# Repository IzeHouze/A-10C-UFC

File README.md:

# A-10C-UFC
DCS A-10C UFC

This project is basically a home grown attempt to create a functional UFC for the A-10C module of the flight sim DCS World.
It is based on a simple 6x6 keyboard matrix interfaced to the PC via an Arduino Microcontroller.  There are the wiring scematics, a PCB layout and Blender files for an enclosure which should be 3D printable.

The PCB has sockets for plug in capability of either the Uno or Nano variety of Arduino Controller.

The code was originally created to work specifically for the A-10C module, however, since the F/A-18 simulation also has a UFC, there is an optional connection for a switch which can be used to change modes between the A-10 and the F-18.  There is also a connector for an external reset switch, which would be best used once you change aircraft modes, reset the controller to have it reboot into the correct mode.

The required software would be:
  DCS-BIOS, preferably the branch that includes the F/A-18 support
  Arduino Studio
      Keypad Library for Arduino - Authors:  Mark Stanley, Alexander Brevig
      DCS-BIOS-Arduino Library 
        Original version - http://dcs-bios.a10c.de/
        Branch with F/A-18 support - https://forums.eagle.ru/showthread.php?t=210960
        
Optional software would be:
  KiCAD - for the schematics and PCB layout
  Blender - for the 3D printable components of an enclosure

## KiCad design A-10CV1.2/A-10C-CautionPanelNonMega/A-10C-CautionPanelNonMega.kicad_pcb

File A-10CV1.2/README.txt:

This is designed in KiCAD 5.0.4

Front panel included using Front Panel Designer.

Both of these applications are free.

These are as-is and are not guaranteed.

In fact this is the 1.1 revision.
A noob mistake I found was that you cannot use Digital pins 0 and 1 if you use this card on a serial 
port, as those are Transmit and Receive for the USB COM port.

I have revised the schematics and layout to move those IOs to A0 and A1 on J3.

I have also added in the connections for a NANO.

And two JST connectors for an external reset button and a Mode selector switch for A-10 and F-18.

Happy BRRRRTing!

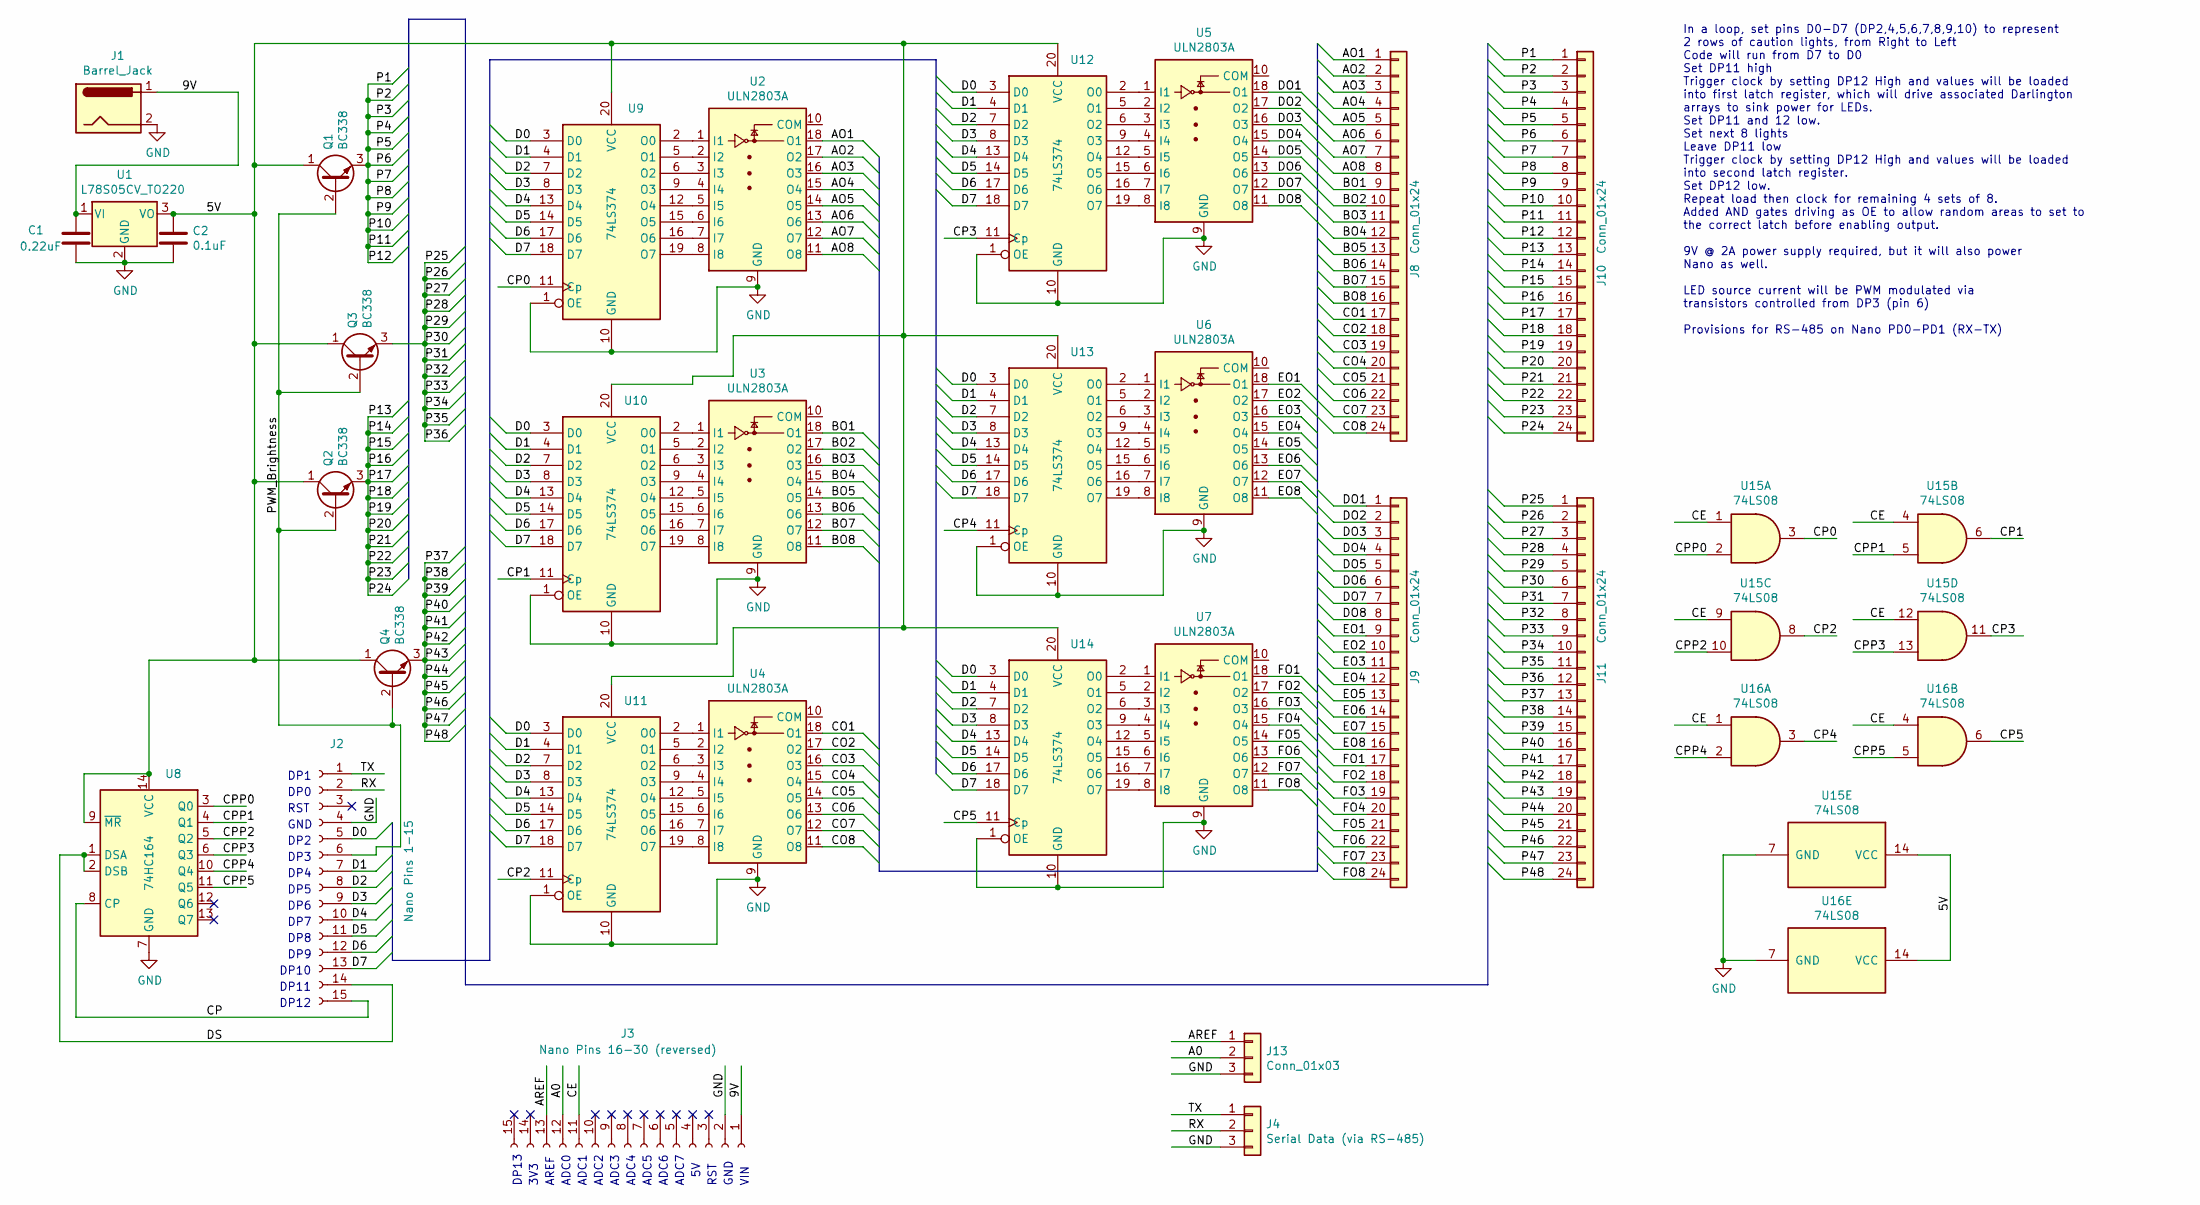
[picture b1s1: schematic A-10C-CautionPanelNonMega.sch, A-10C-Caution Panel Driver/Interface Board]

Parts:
C1: 0.22uF; C_Disc_D3.0mm_W2.0mm_P2.50mm
C2: 0.1uF; C_Disc_D3.0mm_W2.0mm_P2.50mm
J1: Barrel_Jack; BarrelJack_CUI_PJ-102AH_Horizontal
J2: Nano Pins 1-15; PinSocket_1x15_P2.54mm_Vertical
J3: Nano Pins 16-30 (reversed); PinSocket_1x15_P2.54mm_Vertical
J4: Serial Data (via RS-485); PinHeader_1x03_P2.54mm_Vertical
J8, J9, J10, J11: Conn_01x24; PinHeader_1x24_P2.54mm_Vertical
J13: Conn_01x03; PinHeader_1x03_P2.54mm_Vertical
Q1, Q2, Q3, Q4: BC338; TO-92_Inline
U1: L78S05CV_TO220; TO-220-3_Vertical
U2, U3, U4, U5, U6, U7: ULN2803A; DIP-18_W7.62mm
U8: 74HC164; DIP-14_W7.62mm
U9, U10, U11, U12, U13, U14: 74LS374; DIP-20_W7.62mm
U15, U16: 74LS08; DIP-14_W7.62mm

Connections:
/5V: C2.1, Q1.1 (C), Q2.1 (C), Q3.1 (C), Q4.1 (C), U1.3 (VO), U8.9 (~MR), U8.14 (VCC), U9.20 (VCC), U10.20 (VCC), U11.20 (VCC), U12.20 (VCC), U13.20 (VCC), U14.20 (VCC), U15.14 (VCC), U16.14 (VCC)
/9V: C1.1, J1.1, J3.1, U1.1 (VI)
/A0: J3.12, J13.2
/AO1: J8.1, U2.18 (O1)
/AO2: J8.2, U2.17 (O2)
/AO3: J8.3, U2.16 (O3)
/AO4: J8.4, U2.15 (O4)
/AO5: J8.5, U2.14 (O5)
/AO6: J8.6, U2.13 (O6)
/AO7: J8.7, U2.12 (O7)
/AO8: J8.8, U2.11 (O8)
/AREF: J3.13, J13.1
/BO1: J8.9, U3.18 (O1)
/BO2: J8.10, U3.17 (O2)
/BO3: J8.11, U3.16 (O3)
/BO4: J8.12, U3.15 (O4)
/BO5: J8.13, U3.14 (O5)
/BO6: J8.14, U3.13 (O6)
/BO7: J8.15, U3.12 (O7)
/BO8: J8.16, U3.11 (O8)
/CE: J3.11, U15.1, U15.4, U15.9, U15.12, U16.1, U16.4
/CO1: J8.17, U4.18 (O1)
/CO2: J8.18, U4.17 (O2)
/CO3: J8.19, U4.16 (O3)
/CO4: J8.20, U4.15 (O4)
/CO5: J8.21, U4.14 (O5)
/CO6: J8.22, U4.13 (O6)
/CO7: J8.23, U4.12 (O7)
/CO8: J8.24, U4.11 (O8)
/CP: J2.15, U8.8 (CP)
/CP0: U9.11 (Cp), U15.3
/CP1: U10.11 (Cp), U15.6
/CP2: U11.11 (Cp), U15.8
/CP3: U12.11 (Cp), U15.11
/CP4: U13.11 (Cp), U16.3
/CP5: U14.11 (Cp), U16.6
/CPP0: U8.3 (Q0), U15.2
/CPP1: U8.4 (Q1), U15.5
/CPP2: U8.5 (Q2), U15.10
/CPP3: U8.6 (Q3), U15.13
/CPP4: U8.10 (Q4), U16.2
/CPP5: U8.11 (Q5), U16.5
/D0: J2.5, U9.3 (D0), U10.3 (D0), U11.3 (D0), U12.3 (D0), U13.3 (D0), U14.3 (D0)
/D1: J2.7, U9.4 (D1), U10.4 (D1), U11.4 (D1), U12.4 (D1), U13.4 (D1), U14.4 (D1)
/D2: J2.8, U9.7 (D2), U10.7 (D2), U11.7 (D2), U12.7 (D2), U13.7 (D2), U14.7 (D2)
/D3: J2.9, U9.8 (D3), U10.8 (D3), U11.8 (D3), U12.8 (D3), U13.8 (D3), U14.8 (D3)
/D4: J2.10, U9.13 (D4), U10.13 (D4), U11.13 (D4), U12.13 (D4), U13.13 (D4), U14.13 (D4)
/D5: J2.11, U9.14 (D5), U10.14 (D5), U11.14 (D5), U12.14 (D5), U13.14 (D5), U14.14 (D5)
/D6: J2.12, U9.17 (D6), U10.17 (D6), U11.17 (D6), U12.17 (D6), U13.17 (D6), U14.17 (D6)
/D7: J2.13, U9.18 (D7), U10.18 (D7), U11.18 (D7), U12.18 (D7), U13.18 (D7), U14.18 (D7)
/DO1: J9.1, U5.18 (O1)
/DO2: J9.2, U5.17 (O2)
/DO3: J9.3, U5.16 (O3)
/DO4: J9.4, U5.15 (O4)
/DO5: J9.5, U5.14 (O5)
/DO6: J9.6, U5.13 (O6)
/DO7: J9.7, U5.12 (O7)
/DO8: J9.8, U5.11 (O8)
/DS: J2.14, U8.1 (DSA), U8.2 (DSB)
/EO1: J9.9, U6.18 (O1)
/EO2: J9.10, U6.17 (O2)
/EO3: J9.11, U6.16 (O3)
/EO4: J9.12, U6.15 (O4)
/EO5: J9.13, U6.14 (O5)
/EO6: J9.14, U6.13 (O6)
/EO7: J9.15, U6.12 (O7)
/EO8: J9.16, U6.11 (O8)
/FO1: J9.17, U7.18 (O1)
/FO2: J9.18, U7.17 (O2)
/FO3: J9.19, U7.16 (O3)
/FO4: J9.20, U7.15 (O4)
/FO5: J9.21, U7.14 (O5)
/FO6: J9.22, U7.13 (O6)
/FO7: J9.23, U7.12 (O7)
/FO8: J9.24, U7.11 (O8)
/P1: J10.1, J10.2, J10.3, J10.4, J10.5, J10.6, J10.7, J10.8, J10.9, J10.10, J10.11, J10.12, Q1.3 (E)
/P13: J10.13, J10.14, J10.15, J10.16, J10.17, J10.18, J10.19, J10.20, J10.21, J10.22, J10.23, J10.24, Q2.3 (E)
/P25: J11.1, J11.2, J11.3, J11.4, J11.5, J11.6, J11.7, J11.8, J11.9, J11.10, J11.11, J11.12, Q3.3 (E)
/P37: J11.13, J11.14, J11.15, J11.16, J11.17, J11.18, J11.19, J11.20, J11.21, J11.22, J11.23, J11.24, Q4.3 (E)
/PWM_Brightness: J2.6, Q1.2 (B), Q2.2 (B), Q3.2 (B), Q4.2 (B)
/RX: J2.2, J4.2
/TX: J2.1, J4.1
GND: C1.2, C2.2, J1.2, J2.4, J3.2, J4.3, J13.3, U1.2 (GND), U2.9 (GND), U3.9 (GND), U4.9 (GND), U5.9 (GND), U6.9 (GND), U7.9 (GND), U8.7 (GND), U9.1 (OE), U9.10 (GND), U10.1 (OE), U10.10 (GND), U11.1 (OE), U11.10 (GND), U12.1 (OE), U12.10 (GND), U13.1 (OE), U13.10 (GND), U14.1 (OE), U14.10 (GND), U15.7 (GND), U16.7 (GND)
unnamed: U2.1 (I1), U9.2 (O0)
unnamed: U2.2 (I2), U9.5 (O1)
unnamed: U2.3 (I3), U9.6 (O2)
unnamed: U2.4 (I4), U9.9 (O3)
unnamed: U2.5 (I5), U9.12 (O4)
unnamed: U2.6 (I6), U9.15 (O5)
unnamed: U2.7 (I7), U9.16 (O6)
unnamed: U2.8 (I8), U9.19 (O7)
unnamed: U3.1 (I1), U10.2 (O0)
unnamed: U3.2 (I2), U10.5 (O1)
unnamed: U3.3 (I3), U10.6 (O2)
unnamed: U3.4 (I4), U10.9 (O3)
unnamed: U3.5 (I5), U10.12 (O4)
unnamed: U3.6 (I6), U10.15 (O5)
unnamed: U3.7 (I7), U10.16 (O6)
unnamed: U3.8 (I8), U10.19 (O7)
unnamed: U4.1 (I1), U11.2 (O0)
unnamed: U4.2 (I2), U11.5 (O1)
unnamed: U4.3 (I3), U11.6 (O2)
unnamed: U4.4 (I4), U11.9 (O3)
unnamed: U4.5 (I5), U11.12 (O4)
unnamed: U4.6 (I6), U11.15 (O5)
unnamed: U4.7 (I7), U11.16 (O6)
unnamed: U4.8 (I8), U11.19 (O7)
unnamed: U5.1 (I1), U12.2 (O0)
unnamed: U5.2 (I2), U12.5 (O1)
unnamed: U5.3 (I3), U12.6 (O2)
unnamed: U5.4 (I4), U12.9 (O3)
unnamed: U5.5 (I5), U12.12 (O4)
unnamed: U5.6 (I6), U12.15 (O5)
unnamed: U5.7 (I7), U12.16 (O6)
unnamed: U5.8 (I8), U12.19 (O7)
unnamed: U6.1 (I1), U13.2 (O0)
unnamed: U6.2 (I2), U13.5 (O1)
unnamed: U6.3 (I3), U13.6 (O2)
unnamed: U6.4 (I4), U13.9 (O3)
unnamed: U6.5 (I5), U13.12 (O4)
unnamed: U6.6 (I6), U13.15 (O5)
unnamed: U6.7 (I7), U13.16 (O6)
unnamed: U6.8 (I8), U13.19 (O7)
unnamed: U7.1 (I1), U14.2 (O0)
unnamed: U7.2 (I2), U14.5 (O1)
unnamed: U7.3 (I3), U14.6 (O2)
unnamed: U7.4 (I4), U14.9 (O3)
unnamed: U7.5 (I5), U14.12 (O4)
unnamed: U7.6 (I6), U14.15 (O5)
unnamed: U7.7 (I7), U14.16 (O6)
unnamed: U7.8 (I8), U14.19 (O7)

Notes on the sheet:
In a loop, set pins D0-D7 (DP2,4,5,6,7,8,9,10) to represent 2 rows of caution lights, from Right to Left Code will run from D7 to D0 Set DP11 high Trigger clock by setting DP12 High and values will be loaded into first latch register, which will drive associated Darlington arrays to sink power for 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
DP3
DP4
DP5
DP6
DP7
DP8
DP9
DP10
GND
DP2
RST
DP0
DP1
DP11
DP12
DP13
3V3
AREF
ADC0
ADC1
ADC2
ADC3
ADC4
ADC5
ADC6
ADC7
VIN

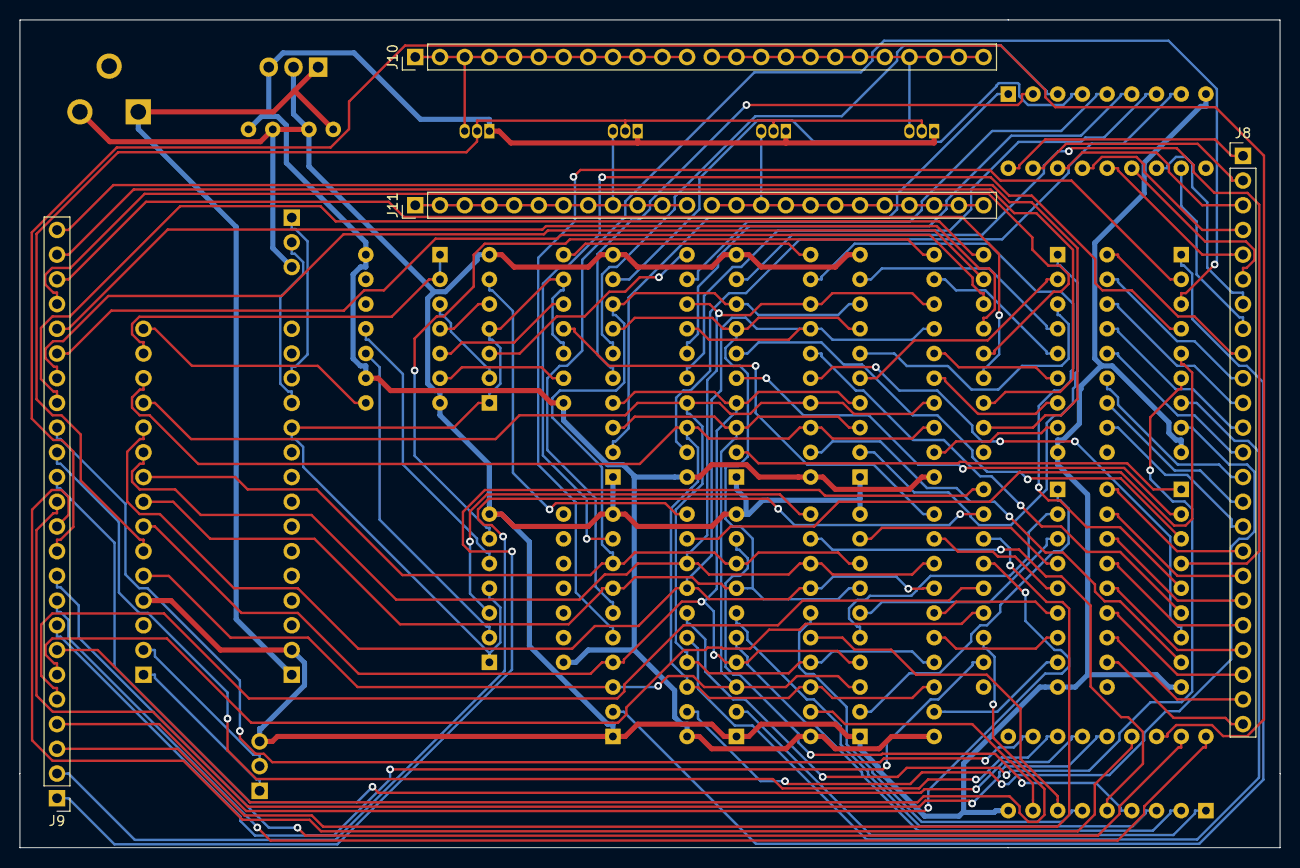
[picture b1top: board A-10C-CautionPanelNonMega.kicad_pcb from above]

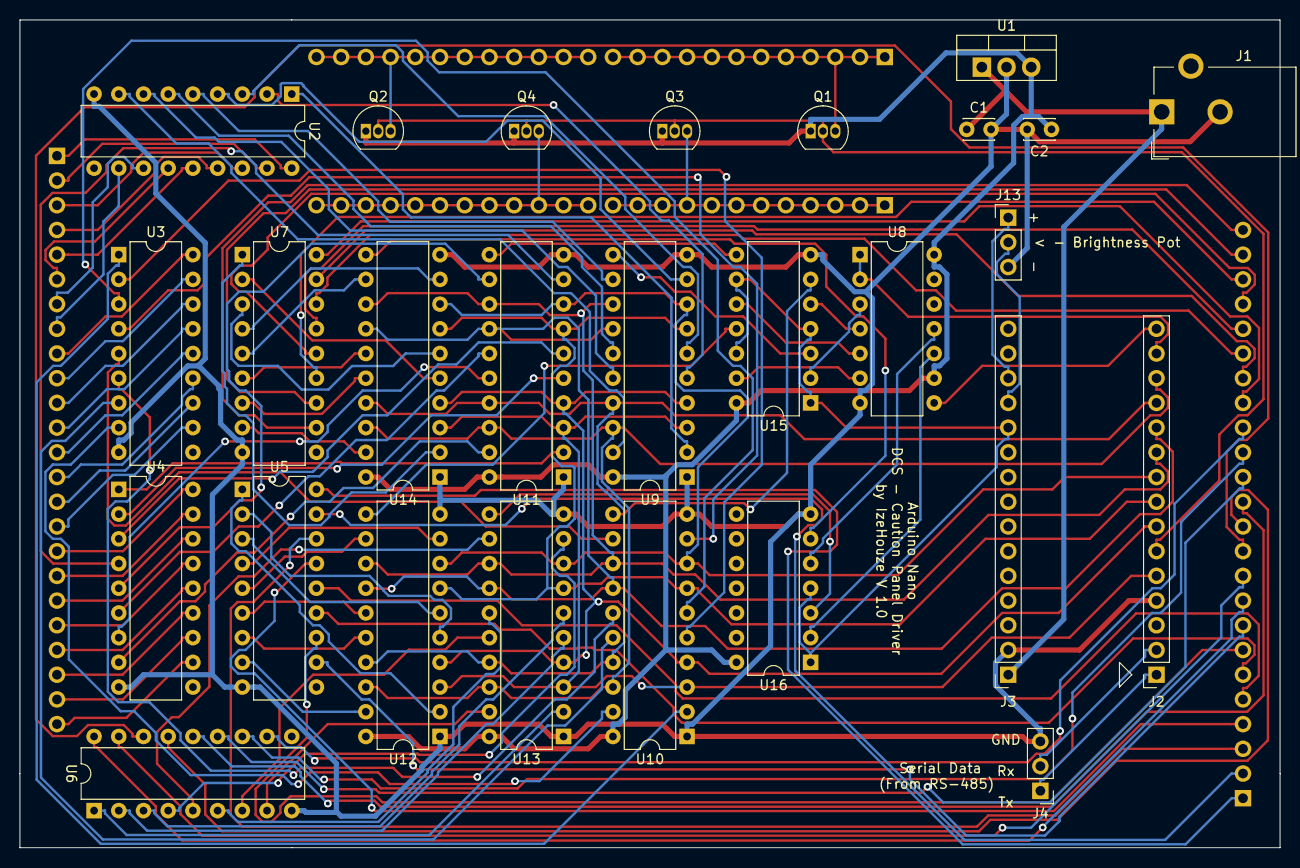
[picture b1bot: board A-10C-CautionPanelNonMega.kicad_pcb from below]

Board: 2 copper layers, 129.5 x 85.1 mm, 31 parts (27 on the bottom side), 131 nets.

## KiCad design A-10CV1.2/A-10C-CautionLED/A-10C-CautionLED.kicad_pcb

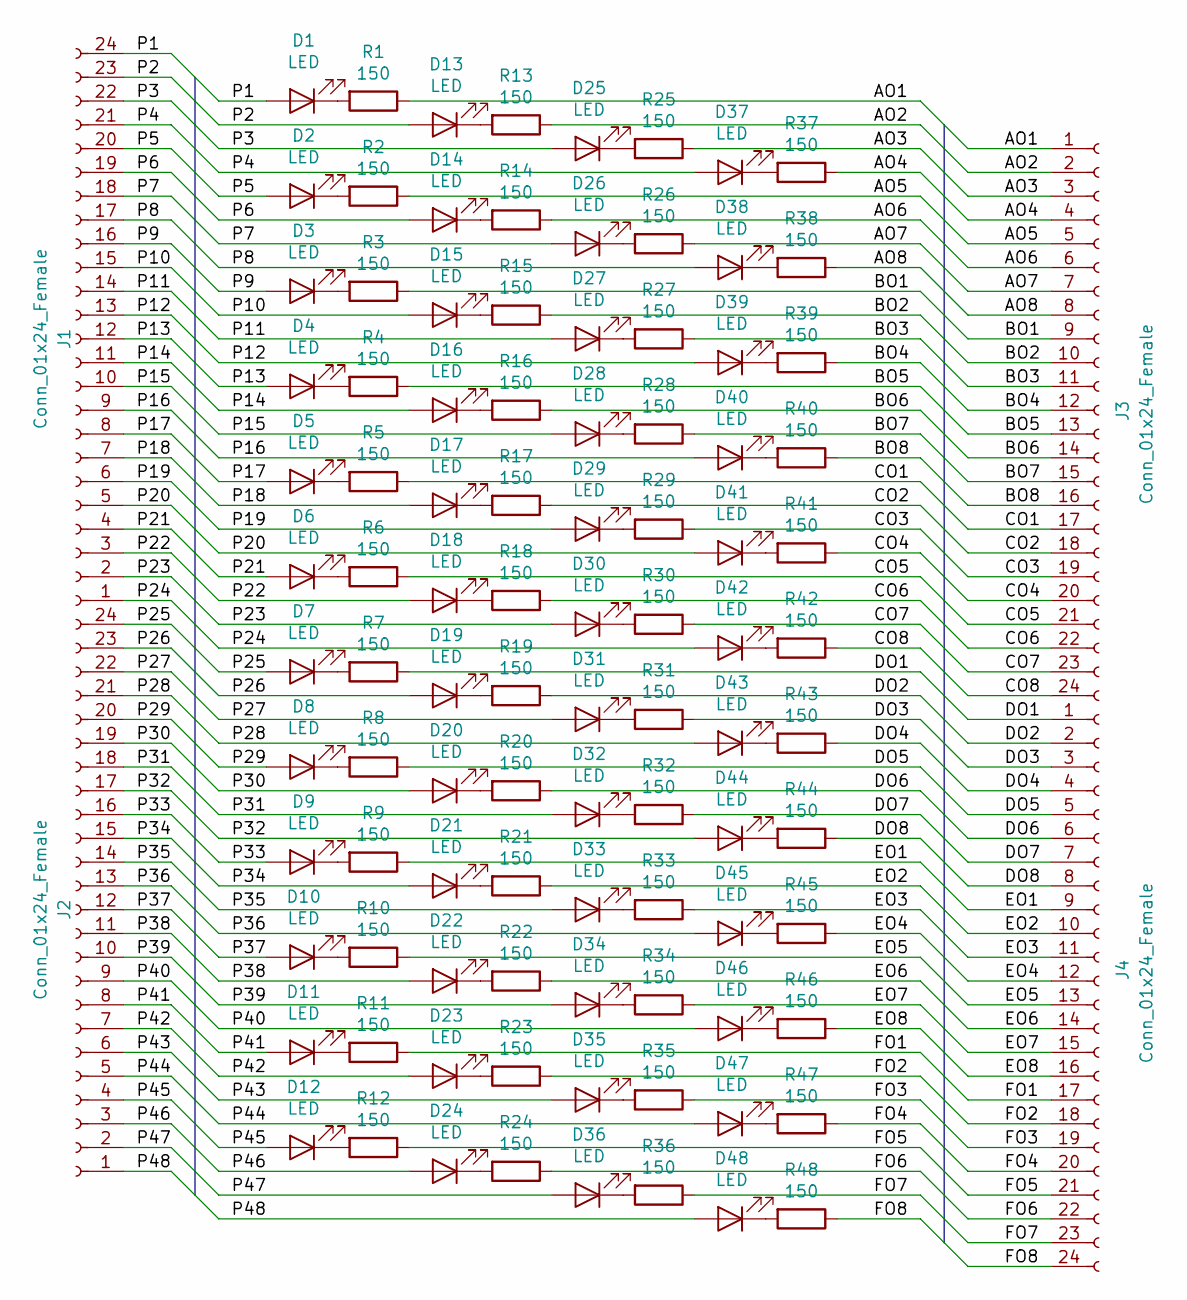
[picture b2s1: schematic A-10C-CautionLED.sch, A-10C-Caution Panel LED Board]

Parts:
D1, D2, D3, D4, D5, D6, D7, D8, D9, D10, D11, D12, D13, D14, D15, D16, D17, D18, D19, D20, D21, D22, D23, D24, D25, D26, D27, D28, D29, D30, D31, D32, D33, D34, D35, D36, D37, D38, D39, D40, D41, D42, D43, D44, D45, D46, D47, D48: LED; LED_D3.0mm
J1, J2, J3, J4: Conn_01x24_Female; PinSocket_1x24_P2.54mm_Vertical
R1, R2, R3, R4, R5, R6, R7, R8, R9, R10, R11, R12, R13, R14, R15, R16, R17, R18, R19, R20, R21, R22, R23, R24, R25, R26, R27, R28, R29, R30, R31, R32, R33, R34, R35, R36, R37, R38, R39, R40, R41, R42, R43, R44, R45, R46, R47, R48: 150; R_Axial_DIN0207_L6.3mm_D2.5mm_P7.62mm_Horizontal

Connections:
/AO1: J3.1, R1.1
/AO2: J3.2, R13.1
/AO3: J3.3, R25.1
/AO4: J3.4, R37.1
/AO5: J3.5, R2.1
/AO6: J3.6, R14.1
/AO7: J3.7, R26.1
/AO8: J3.8, R38.1
/BO1: J3.9, R3.1
/BO2: J3.10, R15.1
/BO3: J3.11, R27.1
/BO4: J3.12, R39.1
/BO5: J3.13, R4.1
/BO6: J3.14, R16.1
/BO7: J3.15, R28.1
/BO8: J3.16, R40.1
/CO1: J3.17, R5.1
/CO2: J3.18, R17.1
/CO3: J3.19, R29.1
/CO4: J3.20, R41.1
/CO5: J3.21, R6.1
/CO6: J3.22, R18.1
/CO7: J3.23, R30.1
/CO8: J3.24, R42.1
/DO1: J4.1, R7.1
/DO2: J4.2, R19.1
/DO3: J4.3, R31.1
/DO4: J4.4, R43.1
/DO5: J4.5, R8.1
/DO6: J4.6, R20.1
/DO7: J4.7, R32.1
/DO8: J4.8, R44.1
/EO1: J4.9, R9.1
/EO2: J4.10, R21.1
/EO3: J4.11, R33.1
/EO4: J4.12, R45.1
/EO5: J4.13, R10.1
/EO6: J4.14, R22.1
/EO7: J4.15, R34.1
/EO8: J4.16, R46.1
/FO1: J4.17, R11.1
/FO2: J4.18, R23.1
/FO3: J4.19, R35.1
/FO4: J4.20, R47.1
/FO5: J4.21, R12.1
/FO6: J4.22, R24.1
/FO7: J4.23, R36.1
/FO8: J4.24, R48.1
/P1: D1.2 (A), J1.24
/P2: D13.2 (A), J1.23
/P3: D25.2 (A), J1.22
/P4: D37.2 (A), J1.21
/P5: D2.2 (A), J1.20
/P6: D14.2 (A), J1.19
/P7: D26.2 (A), J1.18
/P8: D38.2 (A), J1.17
/P9: D3.2 (A), J1.16
/P10: D15.2 (A), J1.15
/P11: D27.2 (A), J1.14
/P12: D39.2 (A), J1.13
/P13: D4.2 (A), J1.12
/P14: D16.2 (A), J1.11
/P15: D28.2 (A), J1.10
/P16: D40.2 (A), J1.9
/P17: D5.2 (A), J1.8
/P18: D17.2 (A), J1.7
/P19: D29.2 (A), J1.6
/P20: D41.2 (A), J1.5
/P21: D6.2 (A), J1.4
/P22: D18.2 (A), J1.3
/P23: D30.2 (A), J1.2
/P24: D42.2 (A), J1.1
/P25: D7.2 (A), J2.24
/P26: D19.2 (A), J2.23
/P27: D31.2 (A), J2.22
/P28: D43.2 (A), J2.21
/P29: D8.2 (A), J2.20
/P30: D20.2 (A), J2.19
/P31: D32.2 (A), J2.18
/P32: D44.2 (A), J2.17
/P33: D9.2 (A), J2.16
/P34: D21.2 (A), J2.15
/P35: D33.2 (A), J2.14
/P36: D45.2 (A), J2.13
/P37: D10.2 (A), J2.12
/P38: D22.2 (A), J2.11
/P39: D34.2 (A), J2.10
/P40: D46.2 (A), J2.9
/P41: D11.2 (A), J2.8
/P42: D23.2 (A), J2.7
/P43: D35.2 (A), J2.6
/P44: D47.2 (A), J2.5
/P45: D12.2 (A), J2.4
/P46: D24.2 (A), J2.3
/P47: D36.2 (A), J2.2
/P48: D48.2 (A), J2.1
unnamed: D1.1 (K), R1.2
unnamed: D2.1 (K), R2.2
unnamed: D3.1 (K), R3.2
unnamed: D4.1 (K), R4.2
unnamed: D5.1 (K), R5.2
unnamed: D6.1 (K), R6.2
unnamed: D7.1 (K), R7.2
unnamed: D8.1 (K), R8.2
unnamed: D9.1 (K), R9.2
unnamed: D10.1 (K), R10.2
unnamed: D11.1 (K), R11.2
unnamed: D12.1 (K), R12.2
unnamed: D13.1 (K), R13.2
unnamed: D14.1 (K), R14.2
unnamed: D15.1 (K), R15.2
unnamed: D16.1 (K), R16.2
unnamed: D17.1 (K), R17.2
unnamed: D18.1 (K), R18.2
unnamed: D19.1 (K), R19.2
unnamed: D20.1 (K), R20.2
unnamed: D21.1 (K), R21.2
unnamed: D22.1 (K), R22.2
unnamed: D23.1 (K), R23.2
unnamed: D24.1 (K), R24.2
unnamed: D25.1 (K), R25.2
unnamed: D26.1 (K), R26.2
unnamed: D27.1 (K), R27.2
unnamed: D28.1 (K), R28.2
unnamed: D29.1 (K), R29.2
unnamed: D30.1 (K), R30.2
unnamed: D31.1 (K), R31.2
unnamed: D32.1 (K), R32.2
unnamed: D33.1 (K), R33.2
unnamed: D34.1 (K), R34.2
unnamed: D35.1 (K), R35.2
unnamed: D36.1 (K), R36.2
unnamed: D37.1 (K), R37.2
unnamed: D38.1 (K), R38.2
unnamed: D39.1 (K), R39.2
unnamed: D40.1 (K), R40.2
unnamed: D41.1 (K), R41.2
unnamed: D42.1 (K), R42.2
unnamed: D43.1 (K), R43.2
unnamed: D44.1 (K), R44.2
unnamed: D45.1 (K), R45.2
unnamed: D46.1 (K), R46.2
unnamed: D47.1 (K), R47.2
unnamed: D48.1 (K), R48.2

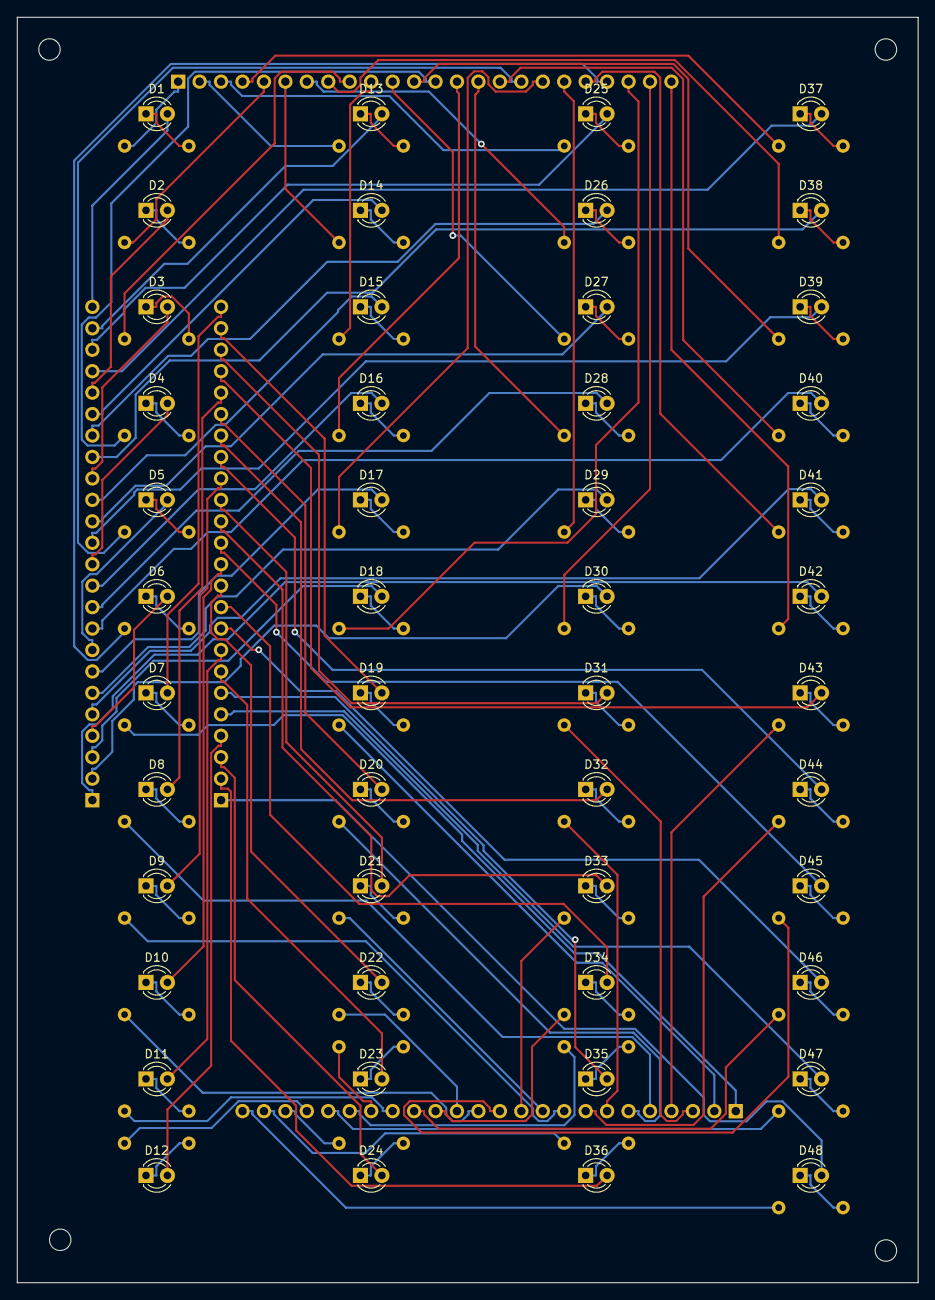
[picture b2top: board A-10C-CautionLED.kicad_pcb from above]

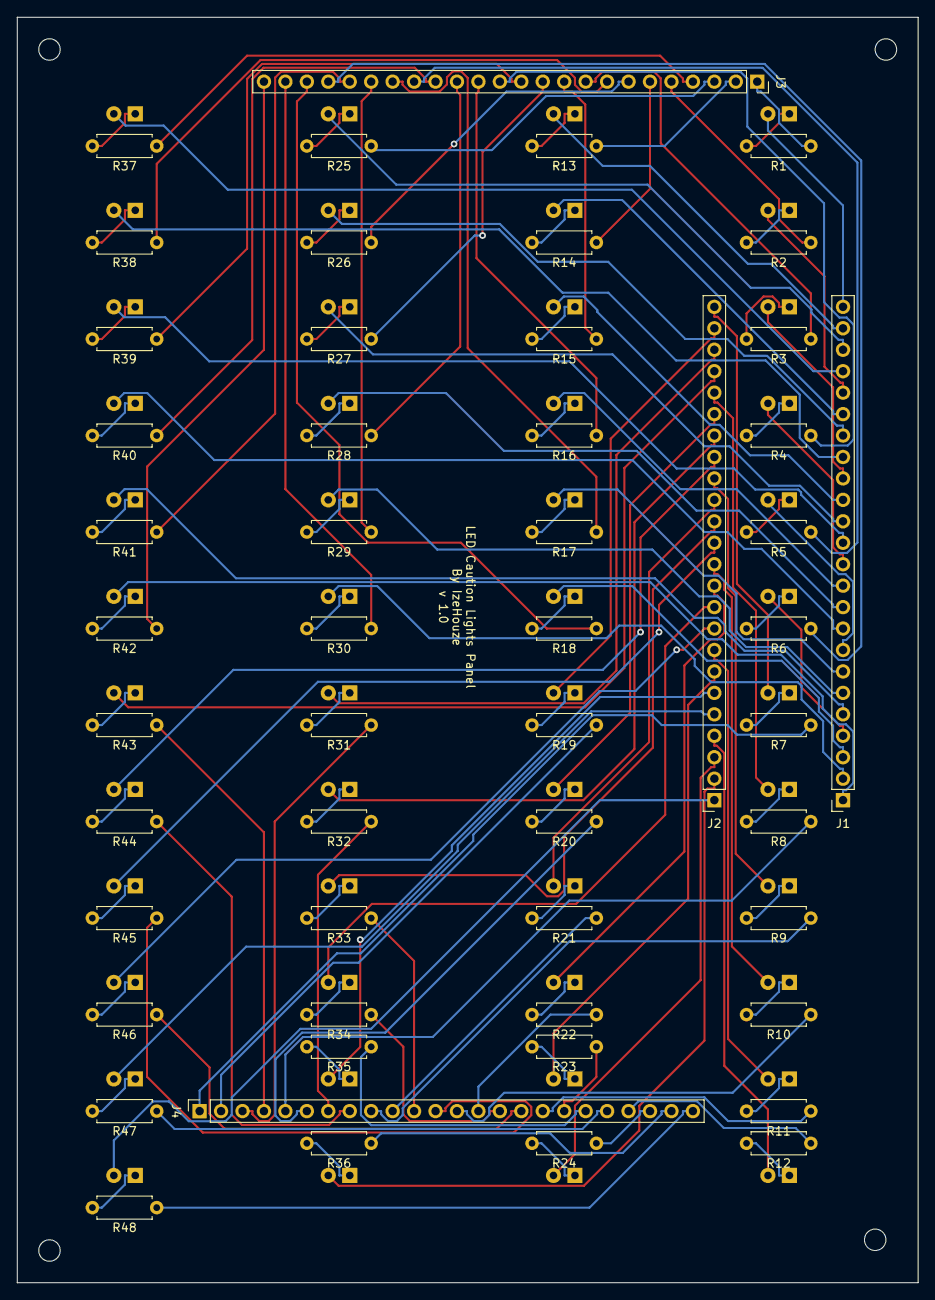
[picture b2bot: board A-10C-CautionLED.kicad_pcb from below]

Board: 2 copper layers, 106.7 x 149.9 mm, 100 parts (52 on the bottom side), 144 nets.

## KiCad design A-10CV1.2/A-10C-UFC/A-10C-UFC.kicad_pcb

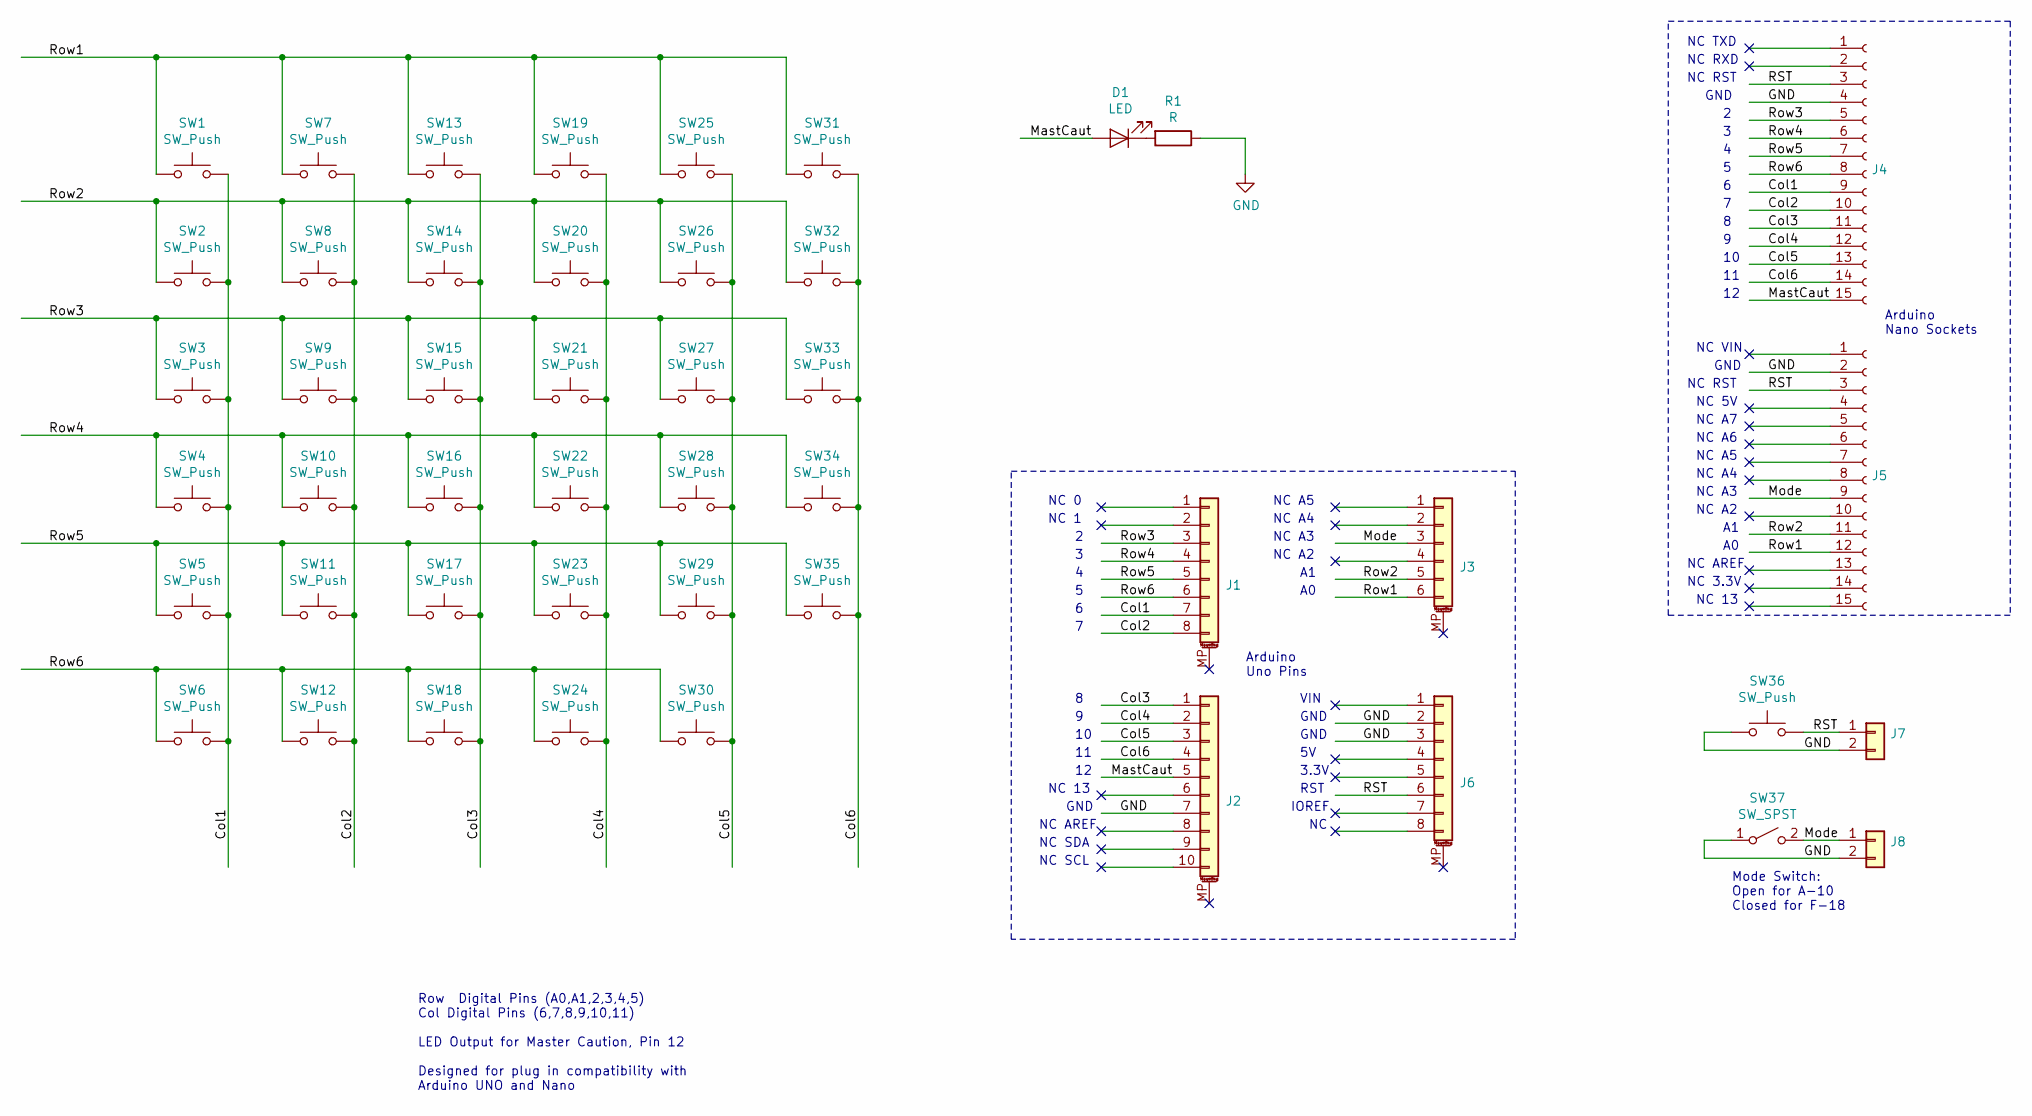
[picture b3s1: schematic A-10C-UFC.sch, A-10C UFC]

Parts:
D1: LED; LED_D3.0mm
J1, J6: Conn_01x08_MountingPin; PinHeader_1x08_P2.54mm_Vertical
J2: Conn_01x10_MountingPin; PinHeader_1x10_P2.54mm_Vertical
J3: Conn_01x06_MountingPin; PinHeader_1x06_P2.54mm_Vertical
J4, J5: Conn_01x15_Female; PinSocket_1x15_P2.54mm_Vertical
J7, J8: Conn_01x02; JST_XH_B02B-XH-A_1x02_P2.50mm_Vertical
R1: R; R_Axial_DIN0207_L6.3mm_D2.5mm_P7.62mm_Horizontal
SW1, SW2, SW3, SW4, SW5, SW6, SW7, SW8, SW9, SW10, SW11, SW12, SW13, SW14, SW15, SW16, SW17, SW18, SW19, SW20, SW21, SW22, SW23, SW24, SW25, SW26, SW27, SW28, SW29, SW30, SW31, SW32, SW33, SW34, SW35: SW_Push; SW_PUSH_6mm
SW36: SW_Push
SW37: SW_SPST

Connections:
/Col1: J1.7, J4.9, SW1.2, SW2.2, SW3.2, SW4.2, SW5.2, SW6.2
/Col2: J1.8, J4.10, SW7.2, SW8.2, SW9.2, SW10.2, SW11.2, SW12.2
/Col3: J2.1, J4.11, SW13.2, SW14.2, SW15.2, SW16.2, SW17.2, SW18.2
/Col4: J2.2, J4.12, SW19.2, SW20.2, SW21.2, SW22.2, SW23.2, SW24.2
/Col5: J2.3, J4.13, SW25.2, SW26.2, SW27.2, SW28.2, SW29.2, SW30.2
/Col6: J2.4, J4.14, SW31.2, SW32.2, SW33.2, SW34.2, SW35.2
/MastCaut: D1.2 (A), J2.5, J4.15
/Mode: J3.3, J5.9, J8.1, SW37.2 (B)
/RST: J4.3, J5.3, J6.6, J7.1, SW36.2
/Row1: J3.6, J5.12, SW1.1, SW7.1, SW13.1, SW19.1, SW25.1, SW31.1
/Row2: J3.5, J5.11, SW2.1, SW8.1, SW14.1, SW20.1, SW26.1, SW32.1
/Row3: J1.3, J4.5, SW3.1, SW9.1, SW15.1, SW21.1, SW27.1, SW33.1
/Row4: J1.4, J4.6, SW4.1, SW10.1, SW16.1, SW22.1, SW28.1, SW34.1
/Row5: J1.5, J4.7, SW5.1, SW11.1, SW17.1, SW23.1, SW29.1, SW35.1
/Row6: J1.6, J4.8, SW6.1, SW12.1, SW18.1, SW24.1, SW30.1
GND: J2.7, J4.4, J5.2, J6.2, J6.3, J7.2, J8.2, R1.1, SW36.1, SW37.1 (A)
unnamed: D1.1 (K), R1.2

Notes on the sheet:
NC 0
NC 1
NC 13
GND
NC AREF
NC SDA
NC SCL
NC A5
NC A4
NC A3
NC A2
NC RST
NC RXD
NC TXD
NC A6
NC A7
NC 3.3V
NC 5V
NC VIN
Arduino Nano Sockets
Arduino Uno Pins
Row Digital Pins (A0,A1,2,3,4,5) Col Digital Pins (6,7,8,9,10,11) LED Output for Master Caution, Pin 12 Designed for plug in compatibility with Arduino UNO and Nano
Mode Switch: Open for A-10 Closed for F-18
VIN
3.3V
RST
IOREF

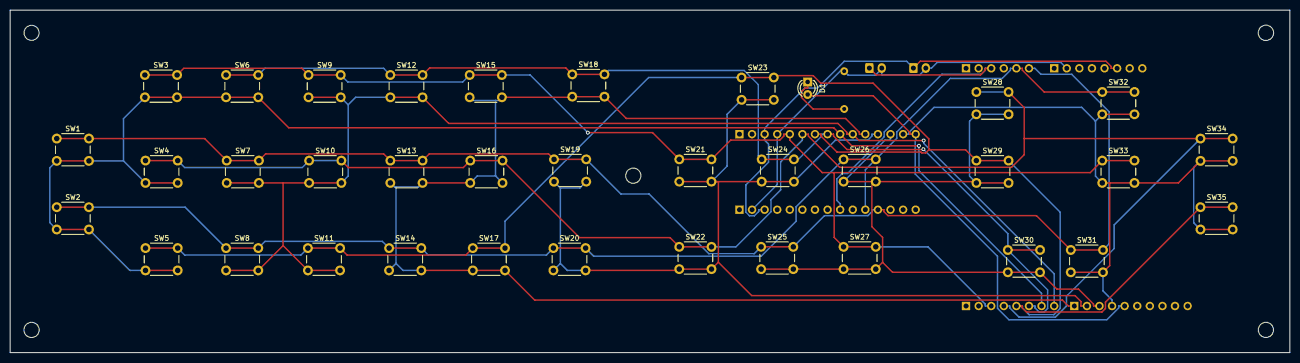
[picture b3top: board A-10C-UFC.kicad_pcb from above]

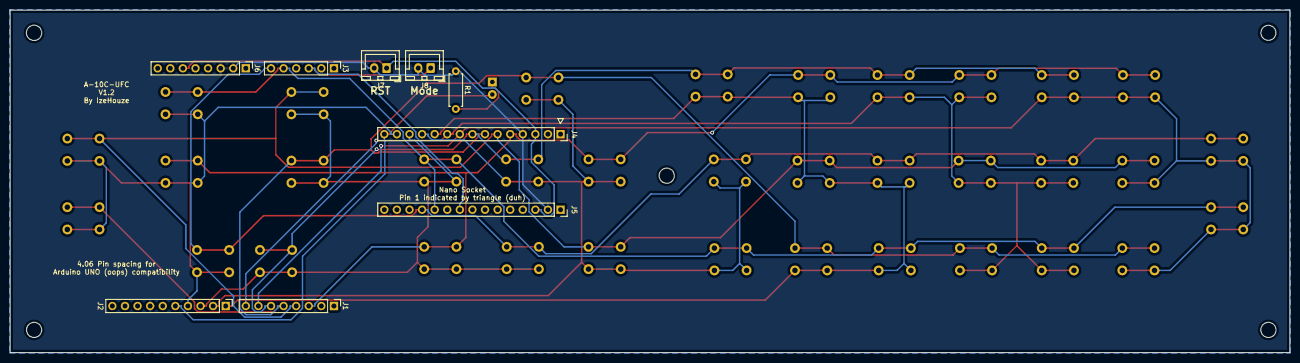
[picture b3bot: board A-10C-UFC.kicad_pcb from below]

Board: 2 copper layers, 258.2 x 69.1 mm, 45 parts (9 on the bottom side), 17 nets.

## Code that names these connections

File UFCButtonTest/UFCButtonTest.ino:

/*  A-10C
  UFC Button Test

  Each press of the buttons will cause the master caution light to light up
  and will go out after release.
*/

#include <Keypad.h>

const int led = 12;
const byte ROWS = 6; // Six rows
const byte COLS = 6; // Six columns

// Define the Keymap
char keys[ROWS][COLS] = {
  {'S', '5', '0', 'M', '$', 'B'},
  {'s', '8', 'c', 'a', '%', 'R'},
  {'1', '3', 'F', '!', '^', 'r'},
  {'4', '6', 'L', '@', 'P', 'D'},
  {'7', '9', 'C', 'e', 'p', 'd'},
  {'2', 'H', 'E', '#', 'b'}
};

// Connect keypad ROW0, ROW1, ROW2 and ROW3 to these Arduino pins.
byte rowPins[ROWS] = { A0, A1, 2, 3, 4, 5 };
// Connect keypad COL0, COL1 and COL2 to these Arduino pins.
byte colPins[COLS] = { 6, 7, 8, 9, 10, 11 };

// Create the Keypad
Keypad kpd = Keypad( makeKeymap(keys), rowPins, colPins, ROWS, COLS );


void setup()
{
  pinMode(led, OUTPUT);
  kpd.addEventListener(keypadEvent);  // Add an event listener.
  kpd.setHoldTime(100);               // Default is 1000mS
  kpd.setDebounceTime(50);           // Default is 50mS
}

void loop()
{
  char key = kpd.getKey();
}

void keypadEvent(KeypadEvent KEY) {
  switch (kpd.getState()) {
    case PRESSED:
      switch (KEY) {

        case 'Z': true; break;
        default: digitalWrite(led, HIGH); break;
      }

  }

  switch (kpd.getState()) {
    case RELEASED:
      switch (KEY) {
        case 'Z': true; break;
        default: digitalWrite(led, LOW); break;
      }
  }
}

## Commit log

2019-08-03 Added KiCAD files and FPD file
2019-08-04 Updated for multi aircraft capability. Added wiring and code.
2019-08-05 Added multi aircraft support code into Arduino
2019-08-05 Corrected some code warnings
2019-08-08 Updated front panel drills points
2019-08-08 Building blender model of case and buttons started.
2019-08-09 More blending
2019-08-09 Updating Models
2019-08-10 Updating everything
2019-08-10 More updates
2019-08-11 Updated to C++ code compliant
2019-08-11 just refining the mode for symetry
2019-08-12 Expanded README content
2019-08-12 Corrected version number to 1.2
2019-08-12 more revisions
2019-08-13 Fixing holes in model?
2019-08-13 Always tweaking board shapes.
2019-08-16 Updated PCB to move headers further inboard from edge
2019-08-16 Forgot some
2019-08-18 Always finding little imperfections.
2019-09-11 Fixed Pins for final version with live board.
2019-09-11 Added images of first ordered results
2019-09-12 Found a weird bug that strcpy on the Master Caution causes certain keys to stop reading in F-18 mode. Switched it to an improper pointer/variable, and it works fine.
2019-09-12 Forgot to remove test code.
2019-09-13 Added flash counter to indicate mode. A-10 = 2 flashes F-18 = 4 flashes.
2019-09-14 Adding some docs
2019-09-14 Cleaning up un-needed files.
2019-09-14 More cleanup
2019-09-14 Created a new Case that is considered "Manifold" for printing purposes.
2019-09-15 Adjusted blender mode stud length to match more closely to real world board dimentions.
2019-09-18 Created quick button LED test sketch.
2019-09-18 Recommitting
2019-09-18 Cleanup
2019-09-18 Fixed copi pasta issues.
2019-10-26 Added new designs for a Caution Lights Panel.
2019-10-28 First bits of working code completed. May be changed in favor of single event vs 48 events.
2019-10-28 Switched to using the IntegerBuffer to get all of the Caution Light values instead of individual calls.
2019-10-28 Correct regulator model
2019-10-29 Updated code for DCS Panels branch of code to match new DCS-BIOS Branch. Updated the FA-18 Master Caution light address. Updated the UFC 0 key to UFC_0 for the FA-18. Added switch mode code for the d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
2019-11-05 Tweaking timing for Nano to 8 bit interface.
2019-11-05 I can math...
2019-11-06 Functional code at this point
2019-11-06 Updated Anano Pin Labels
2019-11-06 Updating RS port to three pin
2019-11-27 Saving before PC reset
2020-07-28 Updated Blender files. New code for new multi aircraft support in DCS-BIOS
2020-08-03 Added a sample export STL of the UFC Case
